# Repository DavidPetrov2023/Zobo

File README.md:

# Zobo - ESP32 BLE Robot Controller

ESP32 robot ovládaný přes Bluetooth Low Energy s Flutter aplikací pro Android.

## Struktura

```
Zobo/
├── zobo_flutter/    # Flutter mobilní aplikace
├── zobo_esp32/      # ESP-IDF firmware
└── zobo_eagle/      # Návrh PCB
```

## Funkce

- BLE ovládání (Nordic UART Service)
- Duální PWM řízení motorů s plynulou akcelerací
- OTA aktualizace firmware přes vlastní server (`petrovelektronika.cz/robot/`)
- Periodická telemetrie do `/devices/` dashboardu (každých 30s)
- WiFi konfigurace přes BLE
- RGB LED indikace stavu
- Deep sleep s úsporným režimem (~10µA)
- Automatické probouzení a blikání LED každých 10s

## Quick Start

### Flutter aplikace
```bash
cd zobo_flutter
python build_install.py        # Build + instalace + spuštění
python build_install.py -d     # Build s debug logem
python build_install.py -c     # Clean build
```

### ESP32 firmware
```bash
cd zobo_esp32
python build_flash.py          # Build + flash přes USB
python build_flash.py -n       # Jen build (bez flashe)
```

## OTA Release (vlastní server)

Firmware se distribuuje přes `petrovelektronika.cz/robot/`, ne přes GitHub.
Telefonní app stáhne version.json, robot pak stáhne binárku přes URL s tokenem.

### Setup (jednorázově)

1. **Na serveru** v `/var/www/html/.env`:
   ```
   ADMIN_ACCESS_KEY=<sdílený klíč pro admin endpointy>
   OTA_DOWNLOAD_TOKEN=<token pro firmware download>
   ```
2. **Lokálně** vytvoř `zobo_esp32/.env`:
   ```
   ADMIN_ACCESS_KEY=<stejný jako na serveru>
   ```
3. **Ve Flutter** v `lib/pages/settings_page.dart` nastav `otaToken` na hodnotu `OTA_DOWNLOAD_TOKEN`.
4. **Nginx**: `client_max_body_size 16M;` v `/etc/nginx/nginx.conf` (default 1MB stačí na 1.3MB firmware).

### Release flow

```bash
# 1. Bumpni verzi v zobo_esp32/main/ota_manager.h (FIRMWARE_VERSION)
# 2. Build + upload na server v jednom kroku:
cd zobo_esp32
python release_server.py --notes "Changelog popis"

# 3. V telefonní appce: Settings → Check for Updates → Update
#    (ESP stáhne novou binárku ze serveru přes WiFi)
```

Skripty:
- `release_server.py` — build + POST na `/robot/api.php` (aktuální flow)
- `release.py` — starý GitHub Releases flow (ponechán jako fallback, nepoužívat)

### Admin URL

- `https://petrovelektronika.cz/robot/?key=<ADMIN_KEY>` — release management + endpoint URL
- `https://petrovelektronika.cz/devices/?key=<ADMIN_KEY>` — live telemetrie všech zařízení

## Hardware

| Funkce | GPIO |
|--------|------|
| Motor L PWM/DIR | 16, 17 |
| Motor R PWM/DIR | 25, 26 |
| RGB LED (R/G/B) | 27, 14, 12 |
| Main LED | 5 |

## Chování

### Sleep mode
- Po 15s nečinnosti ESP32 přejde do deep sleep
- Každých 10s se probudí, krátce blikne modře a zase usne
- Při připojení aplikace posílá ping každých 5s → ESP32 zůstává vzhůru
- Po odpojení aplikace → 15s timeout → deep sleep

### LED indikace
- **Startup**: Sekvence barev (červená → modrá → zelená → bílá)
- **Sleep blink**: Krátké modré bliknutí každých 10s
- **Připojeno**: Bílá (všechny barvy)

## Požadavky

- ESP-IDF v5.0+
- Flutter SDK 3.0+
- Python 3.8+
- Android telefon s BLE

## Autor

David Petrov

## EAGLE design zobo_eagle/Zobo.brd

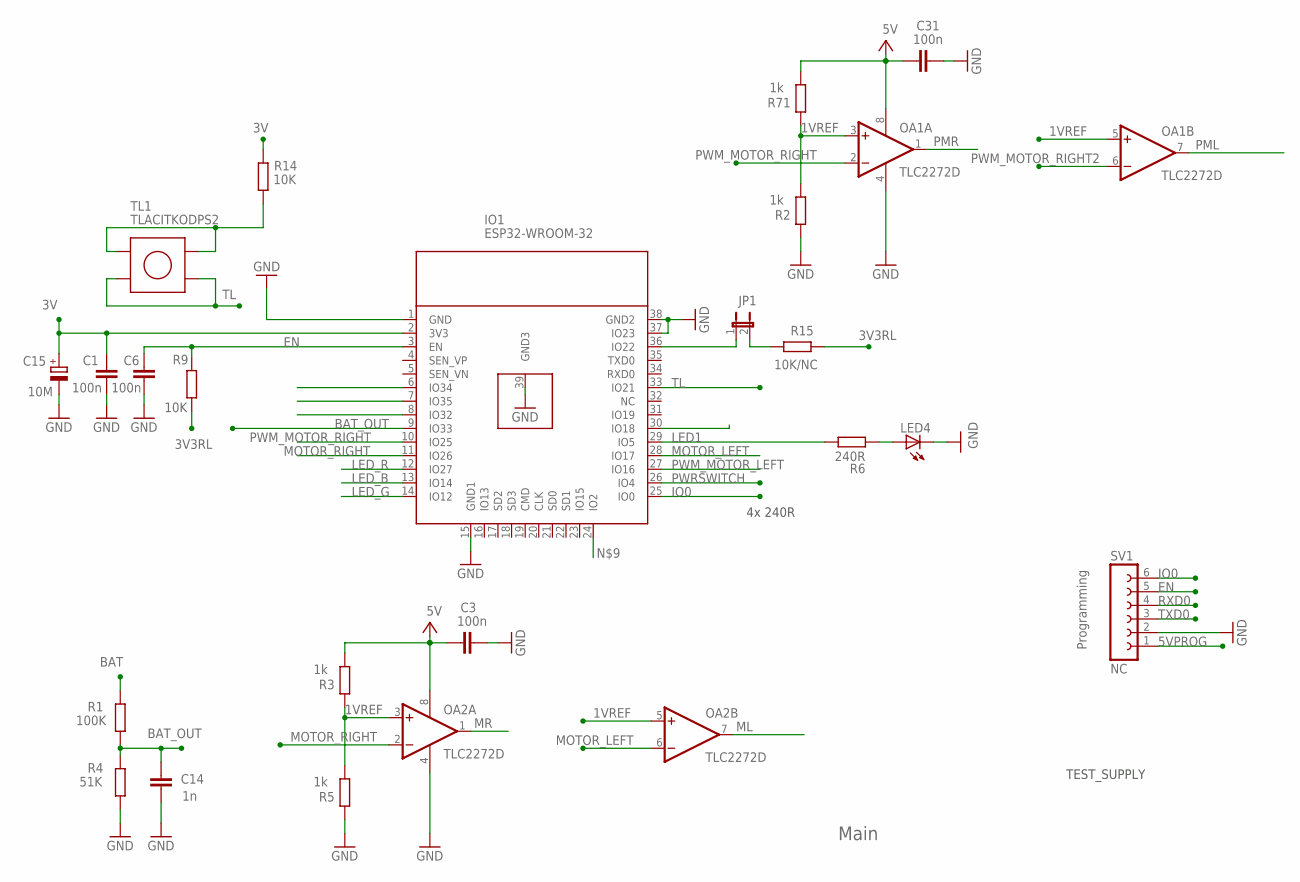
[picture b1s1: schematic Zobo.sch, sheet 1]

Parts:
C1, C3, C6, C31: 100n; C0805
C14: 1n; C0805
C15: 10M; CT3216
IO1: ESP32-WROOM-32
JP1: JP1E; JP1
LED4: LEDCHIPLED_0805; CHIPLED_0805
OA1, OA2: TLC2272D; SO08
R1: 100K; R0805
R2, R3, R5, R71: 1k; R0805
R4: 51K; R0805
R6: 240R; R0805
R9, R14: 10K; R0805
R15: 10K/NC; R0805
SV1: NC; FE06
TL1: TLACITKODPS2; TLACITKO_DPS2

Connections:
1VREF: OA1.3 (+IN), OA1.5 (+IN), OA2.3 (+IN), OA2.5 (+IN), R2.2, R3.1, R5.2, R71.1
3V: C1.2, C15.+, IO1.2 (3V3), R14.2; also elsewhere on the board
3V3RL: R9.2, R15.1
5V: C3.1, C31.1, OA1.8 (V+), OA2.8 (V+), R3.2, R71.2; also elsewhere on the board
5VPROG: SV1.1
BAT: R1.1; also elsewhere on the board
BAT_OUT: C14.2, IO1.9 (IO33), R1.2, R4.1
EN: C6.2, IO1.3 (EN), R9.1, SV1.5
GND: C1.1, C3.2, C6.1, C14.1, C15.-, C31.2, IO1.1 (GND), IO1.15 (GND1), IO1.37 (IO23), IO1.38 (GND2), IO1.39 (GND3), LED4.C, OA1.4 (V-), OA2.4 (V-), R2.1, R4.2, R5.1, SV1.2; also elsewhere on the board
IO0: IO1.25 (IO0), SV1.6
LED1: IO1.29 (IO5), R6.1
LED_B: IO1.13 (IO14)
LED_G: IO1.14 (IO12)
LED_R: IO1.12 (IO27)
ML: OA2.7 (OUT)
MOTOR_LEFT: IO1.28 (IO17), OA2.6 (-IN)
MOTOR_RIGHT: IO1.11 (IO26), OA2.2 (-IN)
MR: OA2.1 (OUT)
unnamed: IO1.36 (IO22), JP1.1
unnamed: JP1.2, R15.2
unnamed: R14.1, TL1.1, TL1.2
unnamed: LED4.A, R6.2
PML: OA1.7 (OUT)
PMR: OA1.1 (OUT)
PWM_MOTOR_LEFT: IO1.27 (IO16)
PWM_MOTOR_RIGHT: IO1.10 (IO25), OA1.2 (-IN)
PWM_MOTOR_RIGHT2: OA1.6 (-IN)
PWRSWITCH: IO1.26 (IO4)
RXD0: SV1.4
TL: IO1.33 (IO21), TL1.3, TL1.4
TXD0: SV1.3

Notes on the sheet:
Main
Programming
4x 240R
TEST_SUPPLY

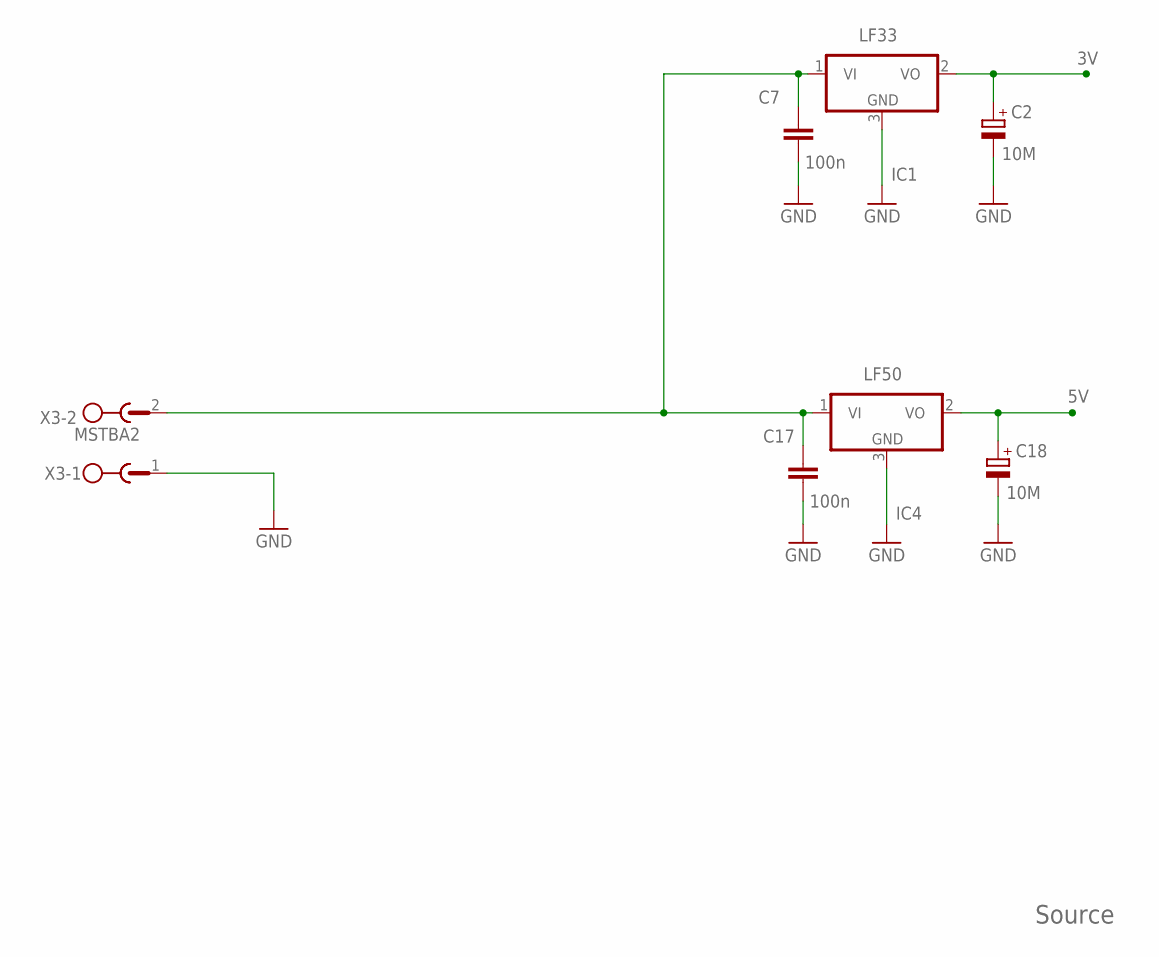
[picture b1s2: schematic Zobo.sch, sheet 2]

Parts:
C2, C18: 10M; CT3216
C7, C17: 100n; C0805
IC1: LF33; TO252
IC4: LF50; TO252
X3: MSTBA2

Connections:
3V: C2.+, IC1.2 (VO); also elsewhere on the board
5V: C18.+, IC4.2 (VO); also elsewhere on the board
BAT: C7.2, C17.2, IC1.1 (VI), IC4.1 (VI), X3.2; also elsewhere on the board
GND: C2.-, C7.1, C17.1, C18.-, IC1.3 (GND), IC4.3 (GND), X3.1; also elsewhere on the board

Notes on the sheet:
Source

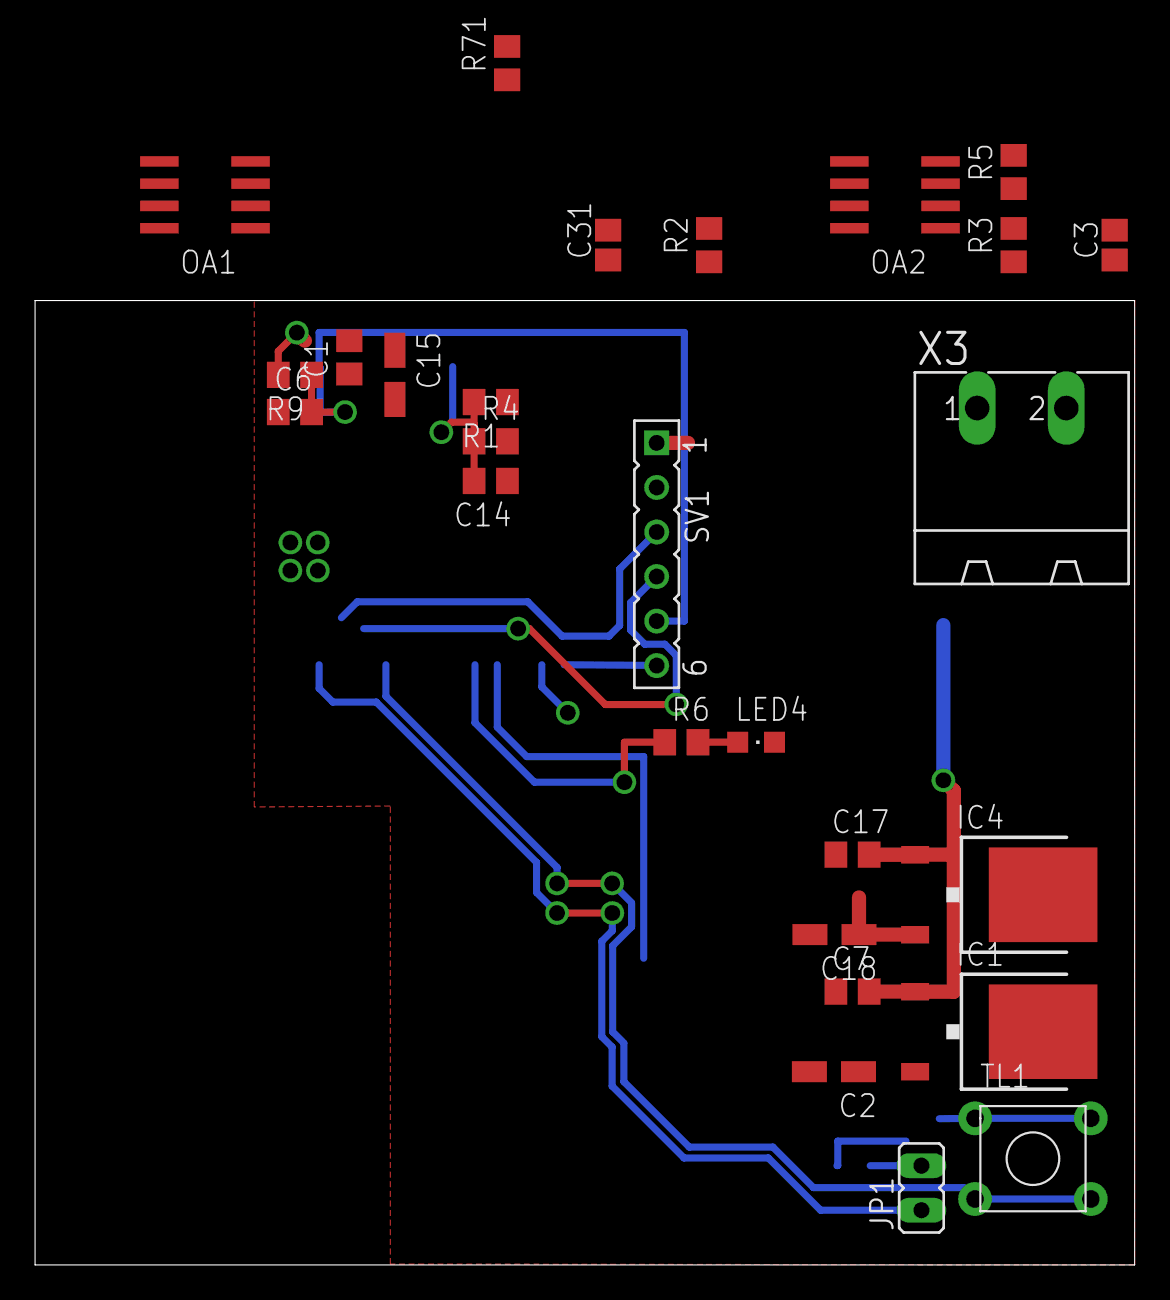
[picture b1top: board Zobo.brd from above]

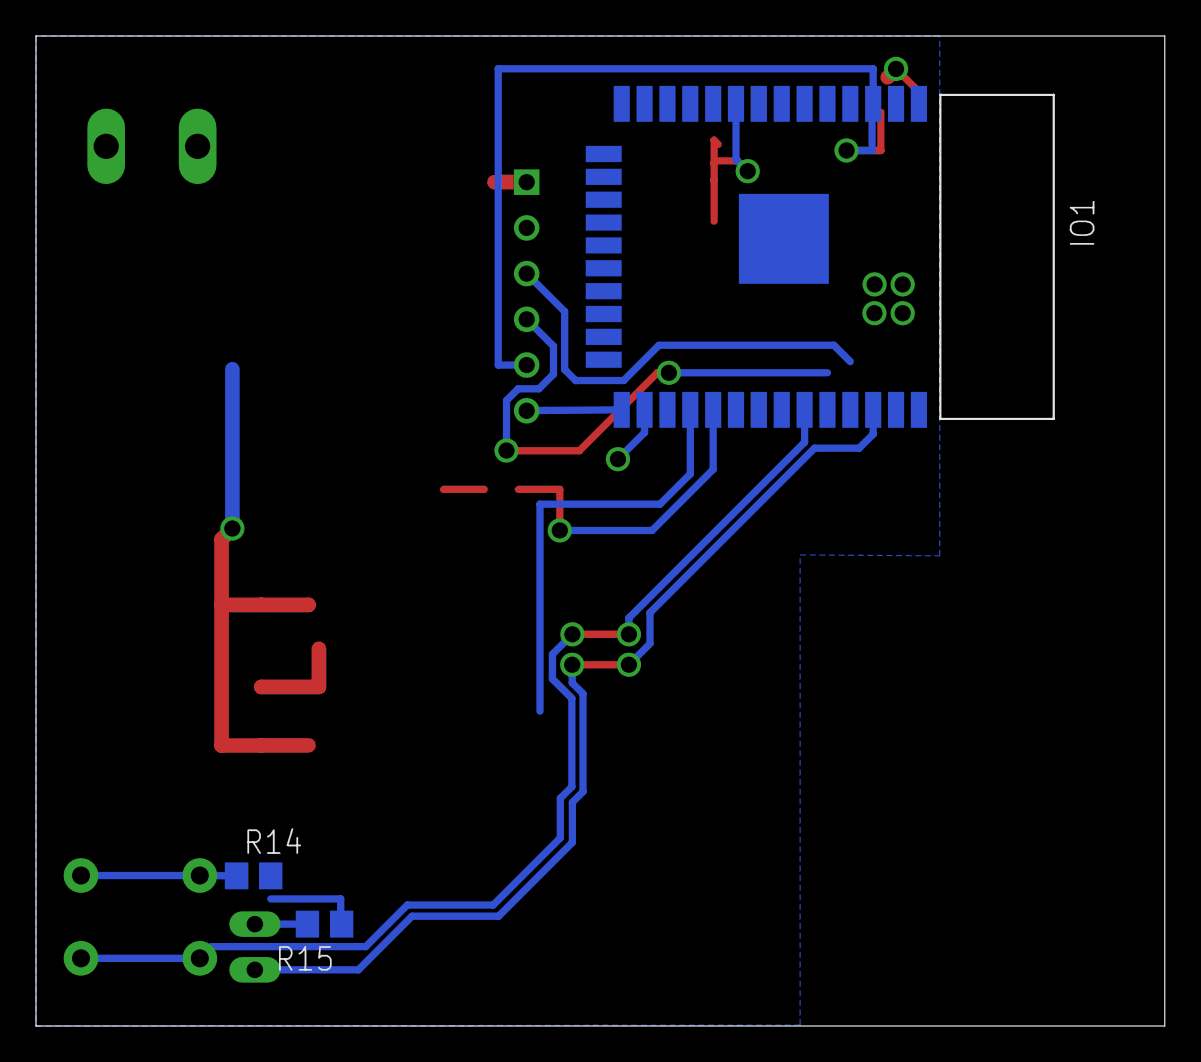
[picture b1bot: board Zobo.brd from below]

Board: 2 copper layers, 62.7 x 55.0 mm, 30 parts (3 on the bottom side), 18 nets.

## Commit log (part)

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2025-12-31 README přeloženo do češtiny
2026-01-02 esp version 1.0.8 release
2026-01-03 old video
2026-01-18 uprava rychlosti pro pasový podvozek
2026-05-21 sleep mode
